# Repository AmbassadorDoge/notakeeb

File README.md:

# This is a Keyboard!

## Description
This is a 65% keyboard that I made to learn more about PCB design & keyboard making! It uses a Raspberry Pi Pico as its microcontroller and I plan to use Akko Penguin switches. On the bottom right of the PCB, there is artwork by [bunnyguy](https://bunnyguy.foo/)!

## Why I Made This
I need a keyboard, and I need to learn pcb design + F360, so why not fulfill both? I also thought this was a fun project, and I learned a lot from researching keyboard components and design! I guess this is a part 2 to the hackpad I made a week earlier.

## Why It's Cool
There are magnets on each side so that decals or wrist rests could be added for customization. There might be keyboard lifts in the making for those side mounts 👀

## Pictures

## BOM
| name        | qty  | price  | link                                                                                                                                                                                                                                                                                                                                                                                                                                                                                                                                                                                                                                                                                                                                                                                                                                                                                                                                                                                                                                                                                                                                                                                                                                                                                                                             | notes                |
| ----------- | ---- | ------ | -------------------------------------------------------------------------------------------------------------------------------------------------------------------------------------------------------------------------------------------------------------------------------------------------------------------------------------------------------------------------------------------------------------------------------------------------------------------------------------------------------------------------------------------------------------------------------------------------------------------------------------------------------------------------------------------------------------------------------------------------------------------------------------------------------------------------------------------------------------------------------------------------------------------------------------------------------------------------------------------------------------------------------------------------------------------------------------------------------------------------------------------------------------------------------------------------------------------------------------------------------------------------------------------------------------------------------- | --------------------- |
| switches    | 2    | 37.98  | [https://www.amazon.com/dp/B0CJY7QN11?maas=maas_adg_38AB58FC53054C4DAC1A347FC7689420_afap_abs&ref_=aa_maas&tag=maas&th=1](https://www.amazon.com/dp/B0CJY7QN11?maas=maas_adg_38AB58FC53054C4DAC1A347FC7689420_afap_abs&ref_=aa_maas&tag=maas&th=1)                                                                                                                                                                                                                                                                                                                                                                                                                                                                                                                                                                                                                                                                                                                                                                                                                                                                                                                                                                                                                                                                               | awesome-mx style      |
| keycaps     | 1    | 20.5   | [https://www.amazon.com/Rainy75-Gradient-Minimalist-Keyboard-Mechanical/dp/B0F5GLMNFS/ref=sxin_27_sbv_search_btf?content-id=amzn1.sym.c8b39f81-ded8-4d75-80c2-6dfa03cbb699%3Aamzn1.sym.c8b39f81-ded8-4d75-80c2-6dfa03cbb699&crid=1MPSXUA5GTUUT&cv_ct_cx=mx%2Bkeycaps%2Bstandard&keywords=mx%2Bkeycaps%2Bstandard&pd_rd_i=B0F5GLMNFS&pd_rd_r=6bb2a6d4-8e5f-4363-8c05-bd323af9282f&pd_rd_w=U4W2a&pd_rd_wg=DZ6HA&pf_rd_p=c8b39f81-ded8-4d75-80c2-6dfa03cbb699&pf_rd_r=G60E95XXVJ1RECAN13DM&qid=1751361425&s=electronics&sbo=RZvfv%2F%2FHxDF%2BO5021pAnSA%3D%3D&sprefix=mx%2Bkeycaps%2Bstandar%2Celectronics%2C154&sr=1-1-5190daf0-67e3-427c-bea6-c72c1df98776&th=1](https://www.amazon.com/Rainy75-Gradient-Minimalist-Keyboard-Mechanical/dp/B0F5GLMNFS/ref=sxin_27_sbv_search_btf?content-id=amzn1.sym.c8b39f81-ded8-4d75-80c2-6dfa03cbb699%3Aamzn1.sym.c8b39f81-ded8-4d75-80c2-6dfa03cbb699&crid=1MPSXUA5GTUUT&cv_ct_cx=mx%2Bkeycaps%2Bstandard&keywords=mx%2Bkeycaps%2Bstandard&pd_rd_i=B0F5GLMNFS&pd_rd_r=6bb2a6d4-8e5f-4363-8c05-bd323af9282f&pd_rd_w=U4W2a&pd_rd_wg=DZ6HA&pf_rd_p=c8b39f81-ded8-4d75-80c2-6dfa03cbb699&pf_rd_r=G60E95XXVJ1RECAN13DM&qid=1751361425&s=electronics&sbo=RZvfv%2F%2FHxDF%2BO5021pAnSA%3D%3D&sprefix=mx%2Bkeycaps%2Bstandar%2Celectronics%2C154&sr=1-1-5190daf0-67e3-427c-bea6-c72c1df98776&th=1) | idk if these work     |
| diodes      | 1    | 5.99   | [https://www.amazon.com/BOJACK-Switching-IN4148-Electronic-Silicon/dp/B07Q4F3Y5W/ref=cm_cr_arp_d_product_top?ie=UTF8](https://www.amazon.com/BOJACK-Switching-IN4148-Electronic-Silicon/dp/B07Q4F3Y5W/ref=cm_cr_arp_d_product_top?ie=UTF8)                                                                                                                                                                                                                                                                                                                                                                                                                                                                                                                                                                                                                                                                                                                                                                                                                                                                                                                                                                                                                                                                                       | first thing popped up |
| board       | 1    | 7.65   | [https://www.digikey.com/en/products/detail/raspberry-pi/SC0918/16627943?gad_source=1&gad_campaignid=20243136172&gbraid=0AAAAADrbLljqW2QWpgmscmTSfeevh5DOv&gclid=Cj0KCQjwyIPDBhDBARIsAHJyyVjjgVDa1KPtyNgtH46oeAumVBSg4IbVCXbjPDwcXYAMfWDoawfxVWUaAt6oEALw_wcB&gclsrc=aw.ds](https://www.digikey.com/en/products/detail/raspberry-pi/SC0918/16627943?gad_source=1&gad_campaignid=20243136172&gbraid=0AAAAADrbLljqW2QWpgmscmTSfeevh5DOv&gclid=Cj0KCQjwyIPDBhDBARIsAHJyyVjjgVDa1KPtyNgtH46oeAumVBSg4IbVCXbjPDwcXYAMfWDoawfxVWUaAt6oEALw_wcB&gclsrc=aw.ds)                                                                                                                                                                                                                                                                                                                                                                                                                                                                                                                                                                                                                                                                                                                                                                           | i think this works    |
| fasteners   | 1    | 9.99   | [https://www.amazon.com/Mywish-Assortment-Stainless-Washers-Wrenche/dp/B0CQQS6STL/ref=sr_1_1_sspa?crid=28SX9XPKU20Q5&dib=eyJ2IjoiMSJ9.dwMblmjxEM9g5HSlEHTddXwVbNEtfIn39mfrWtbe3HEbGWmOpW4nlDGtvjnjUv9lBxON0qfRkqmoCeSFer8UVdyNSpRJWoSjT_lB-2jdiF84ZWBCjpUT8PmkMZyjIyfCbAbFSz7_H3Xv4k2vzIkE7tNEAp1dFILJ9rmj6z9wVtyY1Kh9jt1CyzN8PC_FDJp-wBZtEYo6En2GEzTkSw7FSRCpVCxhf98cmC80X7Ev_rk.X8m8y9LwbooWOW68bzW6-jQ37i08Cq4CkPq6l52Qn8o&dib_tag=se&keywords=nut%2Band%2Bbolt%2Bset%2Bm3%2Bm4&qid=1751223767&sprefix=nut%2Band%2Bbolt%2Bset%2Bm3%2Bm4%2Caps%2C147&sr=8-1-spons&sp_csd=d2lkZ2V0TmFtZT1zcF9hdGY&th=1](https://www.amazon.com/Mywish-Assortment-Stainless-Washers-Wrenche/dp/B0CQQS6STL/ref=sr_1_1_sspa?crid=28SX9XPKU20Q5&dib=eyJ2IjoiMSJ9.dwMblmjxEM9g5HSlEHTddXwVbNEtfIn39mfrWtbe3HEbGWmOpW4nlDGtvjnjUv9lBxON0qfRkqmoCeSFer8UVdyNSpRJWoSjT_lB-2jdiF84ZWBCjpUT8PmkMZyjIyfCbAbFSz7_H3Xv4k2vzIkE7tNEAp1dFILJ9rmj6z9wVtyY1Kh9jt1CyzN8PC_FDJp-wBZtEYo6En2GEzTkSw7FSRCpVCxhf98cmC80X7Ev_rk.X8m8y9LwbooWOW68bzW6-jQ37i08Cq4CkPq6l52Qn8o&dib_tag=se&keywords=nut%2Band%2Bbolt%2Bset%2Bm3%2Bm4&qid=1751223767&sprefix=nut%2Band%2Bbolt%2Bset%2Bm3%2Bm4%2Caps%2C147&sr=8-1-spons&sp_csd=d2lkZ2V0TmFtZT1zcF9hdGY&th=1)                                                                                                                 | m3 hopefully is good  |
| stabilizers | 1    | 18.99  | [https://www.amazon.com/DUROCK-Stabilizers-Translucent-Keyboard-Mechanical/dp/B0B2RVN19F?th=1](https://www.amazon.com/DUROCK-Stabilizers-Translucent-Keyboard-Mechanical/dp/B0B2RVN19F?th=1)                                                                                                                                                                                                                                                                                                                                                                                                                                                                                                                                                                                                                                                                                                                                                                                                                                                                                                                                                                                                                                                                                                                                     | suggested             |
| tape        | 1    | 7.99   | [https://www.amazon.com/Resistant-Sublimation-Temperature-Electronics-Polyimide/dp/B07F8TZZ4N/ref=sr_1_8?crid=1A131O0ZI0A4&dib=eyJ2IjoiMSJ9.VtmU-4xp7faGmB9TAb4YB6R3MgDvUpV1I2hQyU8KJj0g17clYM30cK2ObOpCXD4FH6s7DYcNK4i-IA3hbK2z6vk2GZ5VrbKifHq79jHGaMQ2m-NB6ZVbA1BvVIICI0bq2E5WYjy73QGEG1t7xP123QXN1Q5c6wjbP_BdqIgdsPH_R4lY6juEQ7W_60bcTQghakNfk8rFUV1CGcbJF0WP_RfrfeegrOEsmFuQUAn8fKM.r2Q5CB13SL7oY1vxczy3buI1Tz5LTgkngcK19bo0VWw&dib_tag=se&keywords=heat%2Bresistant%2Btap&qid=1751613740&sprefix=heat%2Bresistant%2Btap%2Caps%2C169&sr=8-8&th=1](https://www.amazon.com/Resistant-Sublimation-Temperature-Electronics-Polyimide/dp/B07F8TZZ4N/ref=sr_1_8?crid=1A131O0ZI0A4&dib=eyJ2IjoiMSJ9.VtmU-4xp7faGmB9TAb4YB6R3MgDvUpV1I2hQyU8KJj0g17clYM30cK2ObOpCXD4FH6s7DYcNK4i-IA3hbK2z6vk2GZ5VrbKifHq79jHGaMQ2m-NB6ZVbA1BvVIICI0bq2E5WYjy73QGEG1t7xP123QXN1Q5c6wjbP_BdqIgdsPH_R4lY6juEQ7W_60bcTQghakNfk8rFUV1CGcbJF0WP_RfrfeegrOEsmFuQUAn8fKM.r2Q5CB13SL7oY1vxczy3buI1Tz5LTgkngcK19bo0VWw&dib_tag=se&keywords=heat%2Bresistant%2Btap&qid=1751613740&sprefix=heat%2Bresistant%2Btap%2Caps%2C169&sr=8-8&th=1)                                                                                                                                                                                                                       |                       |
| magnets     | 1    | 4.51   | [https://www.aliexpress.us/item/3256808695821393.html?spm=a2g0o.productlist.main.1.239aKkKsKkKsAv&algo_pvid=da4cebe6-23a7-4951-9348-322e63ce2b99&algo_exp_id=da4cebe6-23a7-4951-9348-322e63ce2b99-0&pdp_ext_f=%7B%22order%22%3A%224582%22%2C%22eval%22%3A%221%22%7D&pdp_npi=4%40dis%21USD%213.63%213.45%21%21%2125.88%2124.58%21%40210312d517517635248016618e064b%2112000047073358390%21sea%21US%216400803500%21X&curPageLogUid=b9BXQ60S78oI&utparam-url=scene%3Asearch%7Cquery_from%3A](https://www.aliexpress.us/item/3256808695821393.html?spm=a2g0o.productlist.main.1.239aKkKsKkKsAv&algo_pvid=da4cebe6-23a7-4951-9348-322e63ce2b99&algo_exp_id=da4cebe6-23a7-4951-9348-322e63ce2b99-0&pdp_ext_f=%7B%22order%22%3A%224582%22%2C%22eval%22%3A%221%22%7D&pdp_npi=4%40dis%21USD%213.63%213.45%21%21%2125.88%2124.58%21%40210312d517517635248016618e064b%2112000047073358390%21sea%21US%216400803500%21X&curPageLogUid=b9BXQ60S78oI&utparam-url=scene%3Asearch%7Cquery_from%3A)                                                                                                                                                                                                                                                                                                                                                 |                       |
| pcb         | 1(5) | 25.04  |                                                                                                                                                                                                                                                                                                                                                                                                                                                                                                                                                                                                                                                                                                                                                                                                                                                                                                                                                                                                                                                                                                                                                                                                                                                                                                                                  |                       |
|             |      | 138.64 | 152.1574

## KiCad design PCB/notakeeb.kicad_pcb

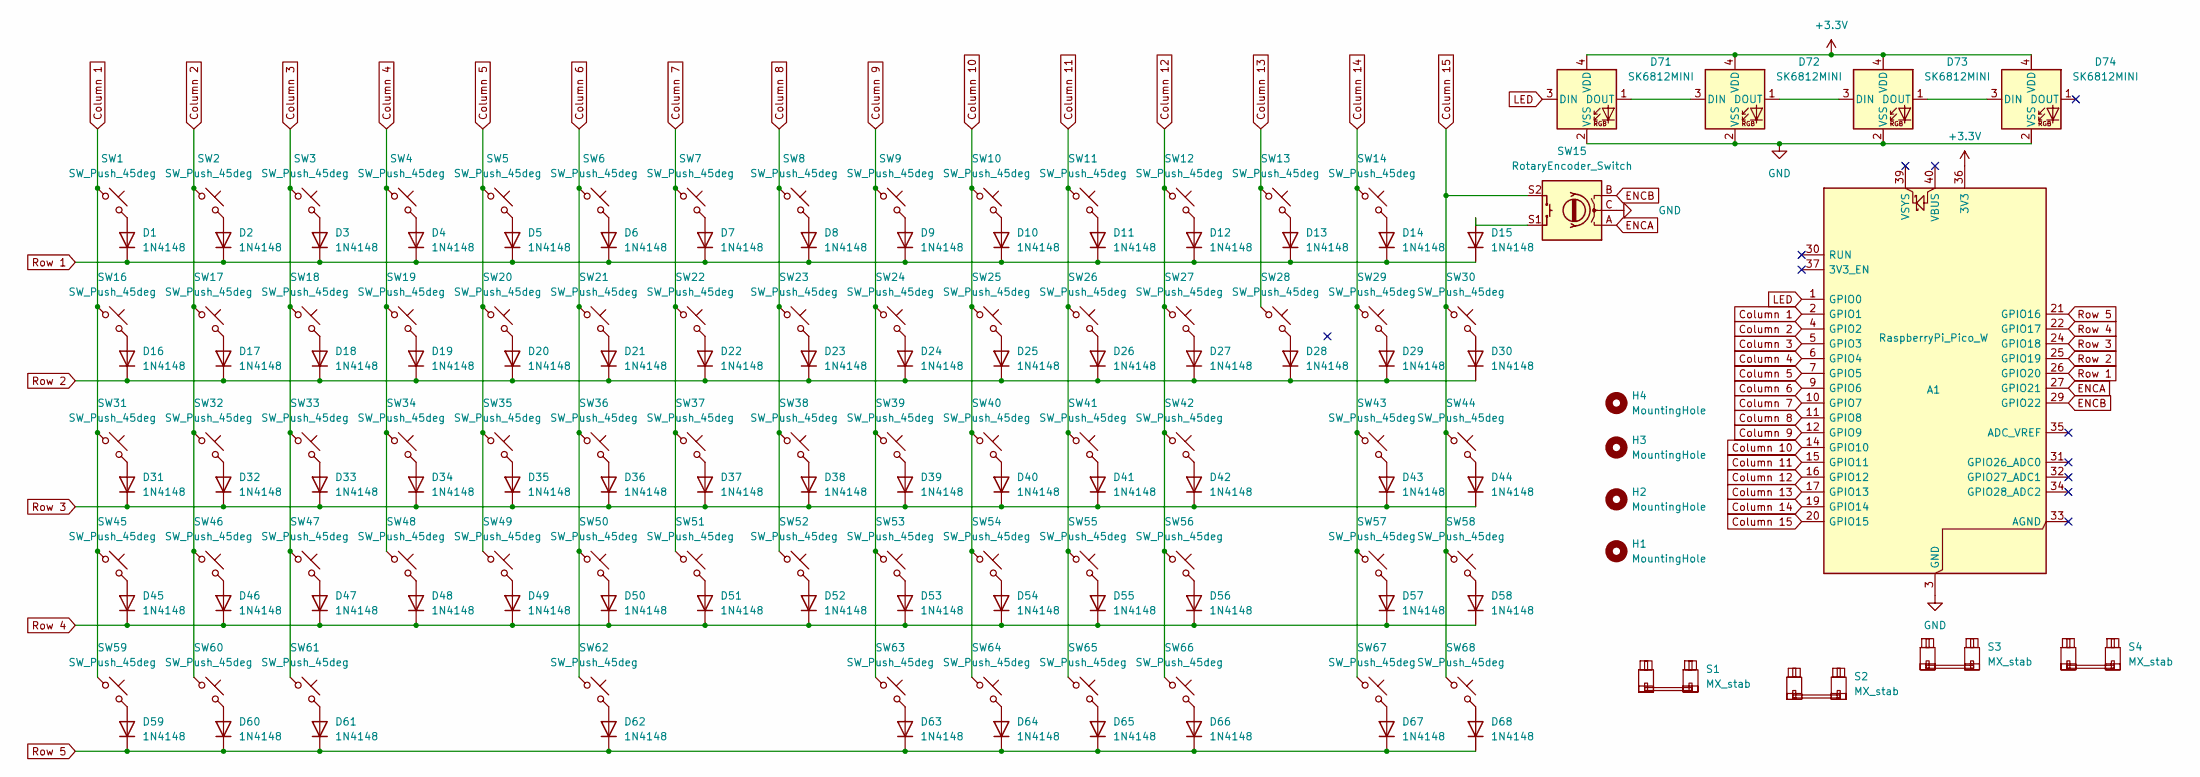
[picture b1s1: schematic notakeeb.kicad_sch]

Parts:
A1: RaspberryPi_Pico_W; RaspberryPi_Pico_Common_THT
D1, D2, D3, D4, D5, D6, D7, D8, D9, D10, D11, D12, D13, D14, D15, D16, D17, D18, D19, D20, D21, D22, D23, D24, D25, D26, D27, D28, D29, D30, D31, D32, D33, D34, D35, D36, D37, D38, D39, D40, D41, D42, D43, D44, D45, D46, D47, D48, D49, D50, D51, D52, D53, D54, D55, D56, D57, D58, D59, D60, D61, D62, D63, D64, D65, D66, D67, D68: 1N4148; D_DO-35_SOD27_P7.62mm_Horizontal
D71, D72, D73, D74: SK6812MINI; LED_SK6812MINI_PLCC4_3.5x3.5mm_P1.75mm
H1, H2, H3, H4: MountingHole; MountingHole_3.2mm_M3_DIN965_Pad_TopBottom
S1, S2, S4: MX_stab; STAB_MX_2u
S3: MX_stab; STAB_MX_6.25u
SW1, SW2, SW3, SW4, SW5, SW6, SW7, SW8, SW9, SW10, SW11, SW12, SW13, SW14, SW16, SW17, SW18, SW19, SW20, SW21, SW22, SW23, SW24, SW25, SW26, SW27, SW28, SW29, SW30, SW31, SW32, SW33, SW34, SW35, SW36, SW37, SW38, SW39, SW40, SW41, SW42, SW43, SW44, SW45, SW46, SW47, SW48, SW49, SW50, SW51, SW52, SW53, SW54, SW55, SW56, SW57, SW58, SW59, SW60, SW61, SW62, SW63, SW64, SW65, SW66, SW67, SW68: SW_Push_45deg; SW_MX_1u
SW15: RotaryEncoder_Switch; RotaryEncoder_Alps_EC11E-Switch_Vertical_H20mm

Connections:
+3.3V: A1.36 (3V3), D71.4 (VDD), D72.4 (VDD), D73.4 (VDD), D74.4 (VDD)
Column 1: A1.2 (GPIO1), SW1.1, SW16.1, SW31.1, SW45.1, SW59.1
Column 2: A1.4 (GPIO2), SW2.1, SW17.1, SW32.1, SW46.1, SW60.1
Column 3: A1.5 (GPIO3), SW3.1, SW18.1, SW33.1, SW47.1, SW61.1
Column 4: A1.6 (GPIO4), SW4.1, SW19.1, SW34.1, SW48.1
Column 5: A1.7 (GPIO5), SW5.1, SW20.1, SW35.1, SW49.1
Column 6: A1.9 (GPIO6), SW6.1, SW21.1, SW36.1, SW50.1, SW62.1
Column 7: A1.10 (GPIO7), SW7.1, SW22.1, SW37.1, SW51.1
Column 8: A1.11 (GPIO8), SW8.1, SW23.1, SW38.1, SW52.1
Column 9: A1.12 (GPIO9), SW9.1, SW24.1, SW39.1, SW53.1, SW63.1
Column 10: A1.14 (GPIO10), SW10.1, SW25.1, SW40.1, SW54.1, SW64.1
Column 11: A1.15 (GPIO11), SW11.1, SW26.1, SW41.1, SW55.1, SW65.1
Column 12: A1.16 (GPIO12), SW12.1, SW27.1, SW42.1, SW56.1, SW66.1
Column 13: A1.17 (GPIO13), SW13.1, SW28.1
Column 14: A1.19 (GPIO14), SW14.1, SW29.1, SW43.1, SW57.1, SW67.1
Column 15: A1.20 (GPIO15), SW15.S2, SW30.1, SW44.1, SW58.1, SW68.1
ENCA: A1.27 (GPIO21), SW15.A
ENCB: A1.29 (GPIO22), SW15.B
GND: A1.3 (GND), A1.8 (GND), A1.13 (GND), A1.18 (GND), A1.23 (GND), A1.28 (GND), A1.38 (GND), D71.2 (VSS), D72.2 (VSS), D73.2 (VSS), D74.2 (VSS), SW15.C
LED: A1.1 (GPIO0), D71.3 (DIN)
unnamed: D1.2 (A), SW1.2
unnamed: D2.2 (A), SW2.2
unnamed: D3.2 (A), SW3.2
unnamed: D4.2 (A), SW4.2
unnamed: D5.2 (A), SW5.2
unnamed: D6.2 (A), SW6.2
unnamed: D7.2 (A), SW7.2
unnamed: D8.2 (A), SW8.2
unnamed: D9.2 (A), SW9.2
unnamed: D10.2 (A), SW10.2
unnamed: D11.2 (A), SW11.2
unnamed: D12.2 (A), SW12.2
unnamed: D13.2 (A), SW13.2
unnamed: D14.2 (A), SW14.2
unnamed: D15.2 (A), SW15.S1
unnamed: D16.2 (A), SW16.2
unnamed: D17.2 (A), SW17.2
unnamed: D18.2 (A), SW18.2
unnamed: D19.2 (A), SW19.2
unnamed: D20.2 (A), SW20.2
unnamed: D21.2 (A), SW21.2
unnamed: D22.2 (A), SW22.2
unnamed: D23.2 (A), SW23.2
unnamed: D24.2 (A), SW24.2
unnamed: D25.2 (A), SW25.2
unnamed: D26.2 (A), SW26.2
unnamed: D27.2 (A), SW27.2
unnamed: D28.2 (A), SW28.2
unnamed: D29.2 (A), SW29.2
unnamed: D30.2 (A), SW30.2
unnamed: D31.2 (A), SW31.2
unnamed: D32.2 (A), SW32.2
unnamed: D33.2 (A), SW33.2
unnamed: D34.2 (A), SW34.2
unnamed: D35.2 (A), SW35.2
unnamed: D36.2 (A), SW36.2
unnamed: D37.2 (A), SW37.2
unnamed: D38.2 (A), SW38.2
unnamed: D39.2 (A), SW39.2
unnamed: D40.2 (A), SW40.2
unnamed: D41.2 (A), SW41.2
unnamed: D42.2 (A), SW42.2
unnamed: D43.2 (A), SW43.2
unnamed: D44.2 (A), SW44.2
unnamed: D45.2 (A), SW45.2
unnamed: D46.2 (A), SW46.2
unnamed: D47.2 (A), SW47.2
unnamed: D48.2 (A), SW48.2
unnamed: D49.2 (A), SW49.2
unnamed: D50.2 (A), SW50.2
unnamed: D51.2 (A), SW51.2
unnamed: D52.2 (A), SW52.2
unnamed: D53.2 (A), SW53.2
unnamed: D54.2 (A), SW54.2
unnamed: D55.2 (A), SW55.2
unnamed: D56.2 (A), SW56.2
unnamed: D57.2 (A), SW57.2
unnamed: D58.2 (A), SW58.2
unnamed: D59.2 (A), SW59.2
unnamed: D60.2 (A), SW60.2
unnamed: D61.2 (A), SW61.2
unnamed: D62.2 (A), SW62.2
unnamed: D63.2 (A), SW63.2
unnamed: D64.2 (A), SW64.2
unnamed: D65.2 (A), SW65.2
unnamed: D66.2 (A), SW66.2
unnamed: D67.2 (A), SW67.2
unnamed: D68.2 (A), SW68.2
unnamed: D71.1 (DOUT), D72.3 (DIN)
unnamed: D72.1 (DOUT), D73.3 (DIN)
unnamed: D73.1 (DOUT), D74.3 (DIN)
Row 1: A1.26 (GPIO20), D1.1 (K), D2.1 (K), D3.1 (K), D4.1 (K), D5.1 (K), D6.1 (K), D7.1 (K), D8.1 (K), D9.1 (K), D10.1 (K), D11.1 (K), D12.1 (K), D13.1 (K), D14.1 (K), D15.1 (K)
Row 2: A1.25 (GPIO19), D16.1 (K), D17.1 (K), D18.1 (K), D19.1 (K), D20.1 (K), D21.1 (K), D22.1 (K), D23.1 (K), D24.1 (K), D25.1 (K), D26.1 (K), D27.1 (K), D28.1 (K), D29.1 (K), D30.1 (K)
Row 3: A1.24 (GPIO18), D31.1 (K), D32.1 (K), D33.1 (K), D34.1 (K), D35.1 (K), D36.1 (K), D37.1 (K), D38.1 (K), D39.1 (K), D40.1 (K), D41.1 (K), D42.1 (K), D43.1 (K), D44.1 (K)
Row 4: A1.22 (GPIO17), D45.1 (K), D46.1 (K), D47.1 (K), D48.1 (K), D49.1 (K), D50.1 (K), D51.1 (K), D52.1 (K), D53.1 (K), D54.1 (K), D55.1 (K), D56.1 (K), D57.1 (K), D58.1 (K)
Row 5: A1.21 (GPIO16), D59.1 (K), D60.1 (K), D61.1 (K), D62.1 (K), D63.1 (K), D64.1 (K), D65.1 (K), D66.1 (K), D67.1 (K), D68.1 (K)

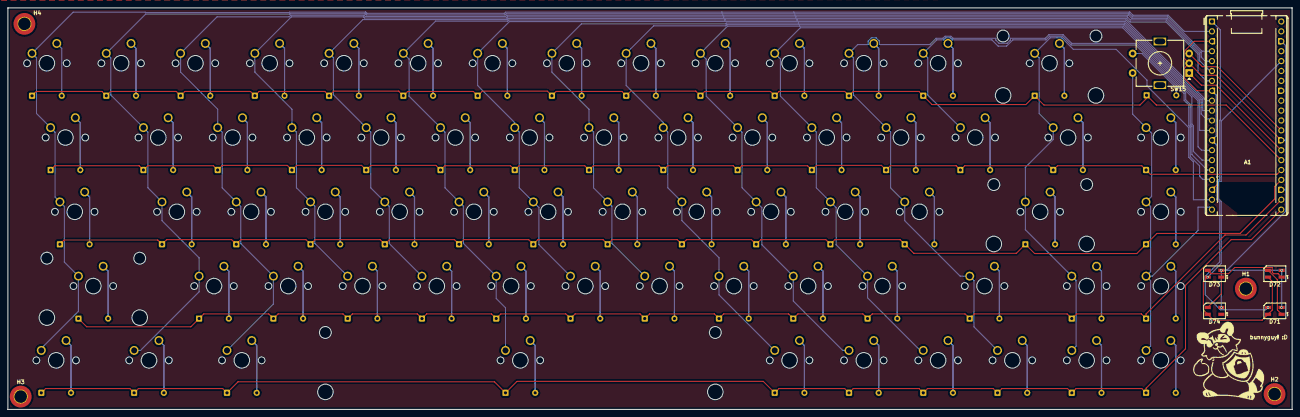
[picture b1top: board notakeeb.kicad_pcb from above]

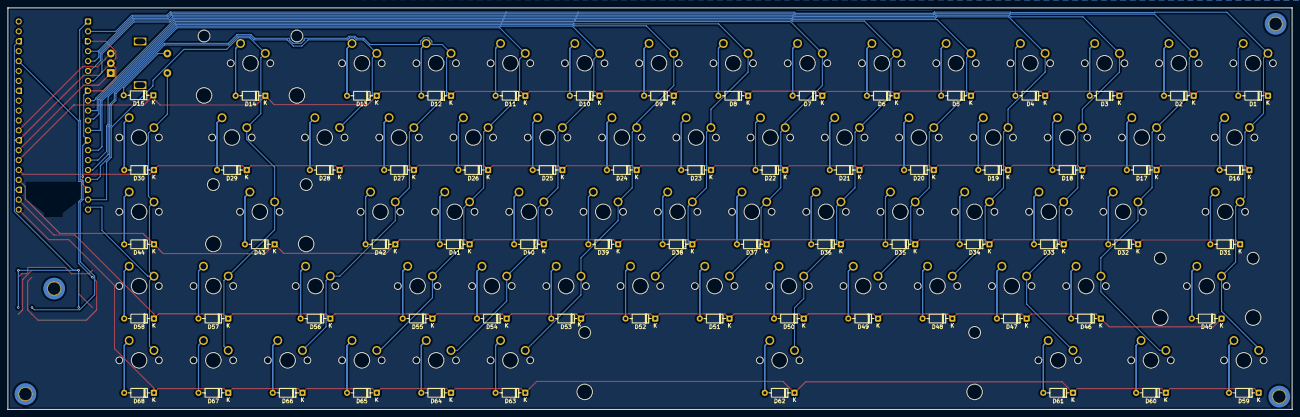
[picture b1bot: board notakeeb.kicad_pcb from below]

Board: 2 copper layers, 329.4 x 103.0 mm, 149 parts (68 on the bottom side), 96 nets.

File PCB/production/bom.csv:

Designator,Footprint,Quantity,Value,LCSC Part #
A1,RaspberryPi_Pico_Common_THT,1,RaspberryPi_Pico_W,
"D1, D10, D11, D12, D13, D14, D15, D16, D17, D18, D19, D2, D20, D21, D22, D23, D24, D25, D26, D27, D28, D29, D3, D30, D31, D32, D33, D34, D35, D36, D37, D38, D39, D4, D40, D41, D42, D43, D44, D45, D46, D47, D48, D49, D5, D50, D51, D52, D53, D54, D55, D56, D57, D58, D59, D6, D60, D61, D62, D63, D64, D65, D66, D67, D68, D7, D8, D9",D_DO-35_SOD27_P7.62mm_Horizontal,68,1N4148,
"D71, D72, D73, D74",LED_SK6812MINI_PLCC4_3.5x3.5mm_P1.75mm,4,SK6812MINI,
"S1, S2, S4",STAB_MX_2u,3,MX_stab,
S3,STAB_MX_6.25u,1,MX_stab,
"SW1, SW10, SW11, SW12, SW13, SW14, SW16, SW17, SW18, SW19, SW2, SW20, SW21, SW22, SW23, SW24, SW25, SW26, SW27, SW28, SW29, SW3, SW30, SW31, SW32, SW33, SW34, SW35, SW36, SW37, SW38, SW39, SW4, SW40, SW41, SW42, SW43, SW44, SW45, SW46, SW47, SW48, SW49, SW5, SW50, SW51, SW52, SW53, SW54, SW55, SW56, SW57, SW58, SW59, SW6, SW60, SW61, SW62, SW63, SW64, SW65, SW66, SW67, SW68, SW7, SW8, SW9",SW_MX_1u,67,SW_Push_45deg,
SW15,RotaryEncoder_Alps_EC11E-Switch_Vertical_H20mm,1,RotaryEncoder_Switch,

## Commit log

2025-07-04 Adding stuff
2025-07-04 Journal additions
2025-07-06 adding fixes
2025-07-06 Add suggestions for approval a
2025-07-07 Added to BOM
2025-07-07 test
